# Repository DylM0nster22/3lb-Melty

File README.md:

# Unschuled dissasembly a 3lb "meltybrain" combat robot

This is a 3lb combat robot that me and luke have designed. this is a special type of robot thats way more complcated then normal bots, normal bots just have normal wheels and then the spinning weapon right well this bot is the weapon, the two hugely overpowered motors act as drive motors set to spin oppisite directions from eachother so the enitre 3lb mass of the robot is the weapon for a greater moi and impact. this can be achieved by using a microcontroller like a arduino nano or in my case a adafruint itsybitsy 32u4 and hooking it to the reciever and allowing it to act as a controller for the motor escs instead of the reciever and what is then does is edit the pwn that the escs get to allow translational drift to happen which is when even when the entire robot is spinning at 5000 rpm it can still go in a mostly stright line. 

# About this project 
This project includes a custom pcb for all the wiring of motors, escs, adafruit and the accelerometer. the pcb also acts as a power distrubution board which i struggled with for a while because of the amount of power going throught it, the back pads of the escs are going to be filled with solder to help conduct the electricity better and allow for more heat disspation. all the vias are also going to be filled to the brim with solder. i also created a reverse polarity protection circuit for the electronics other then the escs using a mosfet. the weapons are going to be made out of ar500 steel for the strength to weight ratio. the pcb is going to cost extra because it has to be 2oz copper, this was a fun and painful project to learn how to make pcbs on. i know buying spares of parts is frowned opon but its the same price without the spare weapon, i also left the carbon fibre out of the bom because theres not enough time to get it quoted.

| Parts                  | Amount | Cost   | Total Cost | Weight     | Total Weight | Provider                                                                                                                                                                                                                                                                                                                                                                                                                                                                                                                                                                                                                       |                                                                |
|------------------------|--------|--------|------------|------------|--------------|--------------------------------------------------------------------------------------------------------------------------------------------------------------------------------------------------------------------------------------------------------------------------------------------------------------------------------------------------------------------------------------------------------------------------------------------------------------------------------------------------------------------------------------------------------------------------------------------------------------------------------|----------------------------------------------------------------|
|                        |        |        |            |            |              |                                                                                                                                                                                                                                                                                                                                                                                                                                                                                                                                                                                                                                |                                                                |
| Drive/Weapon motor     | 2      | $34.59 | $69.18     | 156        | 312          | [HobbyKing](https://hobbyking.com/en_us/propdrive-v2-3542a-1250kv-brushless-outrunner-motor.html)                                                                                                                                                                                                                                                                                                                                                                                                                                                                                                                              | PROPDRIVE v2 3542 1250KV Brushless Outrunner Motor             |
| ESC                    | 2      | $30.00 | $60.00     | 13.9       | 27.8         | [Amazon](https://a.co/d/5kXJAQ6)                                                                                                                                                                                                                                                                                                                                                                                                                                                                                                                                                                                               | HGLRC Specter 90A 8S BLheli32 Single ESC                       |
| Battery                | 1      | $62.99 | $62.99     | 370        | 370          | [Amazon](https://www.amazon.com/OVONIC-Battery-3500mAh-14-8V-Connector/dp/B0DF1V1Z6P/?_encoding=UTF8&pd_rd_w=LSkKY&content-id=amzn1.sym.255b3518-6e7f-495c-8611-30a58648072e%3Aamzn1.symc.a68f4ca3-28dc-4388-a2cf-24672c480d8f&pf_rd_p=255b3518-6e7f-495c-8611-30a58648072e&pf_rd_r=3GX2SF0KEKYJ8BH71HKR&pd_rd_wg=qlzXY&pd_rd_r=9a85c712-36a2-43c4-88b3-a5dd3f800e3c&ref_=pd_hp_d_atf_ci_mcx_mr_ca_hp_atf_d)                                                                                                                                                                                                                   | OVONIC 4S LiPo Battery 3500mAh 14.8V 130C                      |
| Reciever               | 1      | $5.67  | $5.67      | 0.9        | 0.9          | [Aliexpress](https://www.aliexpress.us/item/3256804714662317.html?spm=a2g0o.cart.0.0.6c8138damJGm9i&mp=1&pdp_npi=5%40dis%21USD%21USD%206.16%21USD%206.16%21%21USD%204.16%21%21%21%402101ef7017504365178903148e6532%2112000030953927637%21ct%21US%212956977473%21%211%210&gatewayAdapt=glo2usa)                                                                                                                                                                                                                                                                                                                                 | FS2A 4CH AFHDS 2A                                              |
| Power switch           | 1      | $12.50 | $12.50     | 3          | 3            | [Repeat Robotics](https://repeat-robotics.com/buy/lynx-robot-switch/)                                                                                                                                                                                                                                                                                                                                                                                                                                                                                                                                                          | Lynx Anti-Spark Switch                                         |
| xt90 connector         | 1      | $12.99 | $12.99     | 18         | 36           | [Amazon](https://www.amazon.com/Yaohappy-Female-Bullet-Connectors-Battery/dp/B09L7GVWQ3?crid=2DGTJESIMJTI6&dib=eyJ2IjoiMSJ9.oj1eUX0K8K_T0ur2ZxRGOM_CHZcyffxqSc1sgTjLAVN_I8r0h-obcUxYasMM4pYiOT1-S7qvVRchCayMgTNkU9IHnSKHER11JB_SiyPN9TecKYbwlhtO-RVSU9PrwBjnGgEY4DYm6_s-GeH3TM9wyH8pjgsBidaMcXvCOAYD34LUtqNIVab5L0lMZO6SI-hlTBOQfHdTATIl4dHOiav3BXo8PqcrIy32ZCANfyBYoM-kYA9tz9-Rlfc7lQlCbdrgt_8ZJZdmC50YWCj4fq5Y0-1VINZfEkPBW9dsDkh7r4Y.p3LGtmhXeP_0f3tTEGv2Nu7CnV341Z1n8g0Of38vXMQ&dib_tag=se&keywords=xt180+connector&qid=1753072755&sprefix=xt180connector%2Caps%2C168&sr=8-13)                                             | xt90 connector                                                 |
| Buck Converter         | 1      | $3.55  | $3.55      | 3.85       | 3.85         | [Amazon](https://www.amazon.com/MEIVIFPV-Adjustable-Step-Down-Regulator-Quadcopter/dp/B0FCXTHX6W?crid=390TLPDTMMXZ5&dib=eyJ2IjoiMSJ9.1Jr64zcoS95A1rK3EBxNO3CJIyoZ79mjTwTGw-cGWwYzhsCjnwtq9tFKYtru7VslVwgn9NEwjFYUUAOIaBOdvRIIgADMhHxlZJw0nvxlIHNkWRB8i0TFbIHmy0jwz6bVKr2QxWyVsR5isN6o5xJ9p7NSM2FwncUvSvqxy9yQLel8lqT1HJv0LgqZMGddMUIMBy36P_skSL0CO1tlN3tN3l6ipZThyEs9flVcMkC-wLIvK8ZxHRQ3N3zzW-O-zwQPmJGyHZVmbPB7KdunM6jDycJsjYrUI3pfAjLhtyYeu1w.QzENFgkpZGmEwmCkBdKwvgVK3PpWlenEBpUwdHTDCyk&dib_tag=se&keywords=drone+regulator&qid=1753248899&sprefix=drone+regulato%2Caps%2C159&sr=8-7)                                     | Micro voltage regulator                                        |
| N-Channel mosfet       | 1      | $2.23 | $2.23     | negligible | negligible   | [Aliexpress](https://www.aliexpress.us/item/3256805136051666.html?spm=a2g0o.productlist.main.8.27ed2609oAbEZ7&algo_pvid=d6eaea9b-1818-4388-9122-a9396b72f46d&algo_exp_id=d6eaea9b-1818-4388-9122-a9396b72f46d-7&pdp_ext_f=%7B%22order%22%3A%225%22%2C%22eval%22%3A%221%22%7D&pdp_npi=6%40dis%21USD%212.23%212.23%21%21%2115.90%2115.90%21%402103241117544216774251366e2c2a%2112000032623433723%21sea%21US%212956977473%21X%211%210%21&curPageLogUid=rvZuV4hUFt88&utparam-url=scene%3Asearch%7Cquery_from%3A)                                                                                                                    | N-Channel Enhancement-Mode MOSFET Transistor 60V 115mA,SOT-23. |
| Accelerometer          | 1      | $25    | $25        | Unknown    | Unknown      | [Adafruit](https://www.adafruit.com/product/4627#technical-details)                                                                                                                                                                                                                                                                                                                                                                                                                                                                                                                                                            | Adafruit H3LIS331 Ultra High Range Triple-Axis Accelerometer   |
| Pin headers            | 1      | $1.68  | $1.68     | negligible | negligible   | [Aliexpress](https://www.aliexpress.us/item/2255800801798474.html?spm=a2g0o.productlist.main.1.7e4140cdhZ4fRh&algo_pvid=92aa51d4-414d-4073-8481-74f9170e3e0f&algo_exp_id=92aa51d4-414d-4073-8481-74f9170e3e0f-0&pdp_ext_f=%7B%22order%22%3A%221753%22%2C%22eval%22%3A%221%22%7D&pdp_npi=6%40dis%21USD%211.50%211.47%21%21%211.50%211.47%21%402101ef5e17544215568701003ea1fe%2110000013202368848%21sea%21US%212956977473%21X%211%210%21&curPageLogUid=oNsbEpczPk1e&utparam-url=scene%3Asearch%7Cquery_from%3A)                                                                                                                        | 40 pin Breakable Pin Header                                    |
| P-Channel mosfet       | 1      | $2.83  | $2.83      | negligible | negligible   | [Aliexpress](https://www.aliexpress.us/item/3256807719253034.html?productId=3256807719253034&selectedSkuId=12000042789419948&channel=detailPageDealCombineFloor&combineBizType=platformFreeShipping&intent_extra_sku_from=from_add_to_shopcart&type=mergeorder&pdp_npi=4%40dis%21USD%212.83%21%21%21%212.83%21%21%402101eac917531333647576521ef40e%2112000042789419948%21fus%21US%212956977473%21X&trackParams=%7B%22businessScenario%22%3A%22choiceV2%22%2C%22activityType%22%3A%22CHOICE_FREE_SHIPPING%22%7D&spm=a2g0o.detail.fusionpage.0&gatewayAdapt=glo2usa)                                                             | SUM110P06-07L-E3 p channel mosfet                              |
| Blue LED               | 1      | $ 3.68 | $3.68      | 2.8        | 2.8          | [Aliexpress](https://www.aliexpress.us/item/3256803137393104.html?spm=a2g0o.productlist.main.4.6ec9llDBllDB7Q&aem_p4p_detail=202508022044181770915020208280005830057&algo_pvid=d7b2affc-a5fc-4cad-83a2-7c0d2d7caf38&algo_exp_id=d7b2affc-a5fc-4cad-83a2-7c0d2d7caf38-3&pdp_ext_f=%7B%22order%22%3A%22913%22%2C%22eval%22%3A%221%22%7D&pdp_npi=4%40dis%21USD%213.88%213.68%21%21%213.88%213.68%21%402101c80017541926584706554e918c%2112000025211444658%21sea%21US%212956977473%21X&curPageLogUid=JX9L9FsJ3aNU&utparam-url=scene%3Asearch%7Cquery_from%3A&search_p4p_id=202508022044181770915020208280005830057_1)               | Clear blue LED Diode Lights                                    |
| Zener Diode            | 1      | $2.02  | $2.02      | negligible | negligible   | [Aliexpress](https://www.aliexpress.us/item/3256807042309359.html?spm=a2g0o.productlist.main.3.63b223e0PyMMgl&algo_pvid=0ef8bae5-e9ff-4628-8746-641cc5e44014&algo_exp_id=0ef8bae5-e9ff-4628-8746-641cc5e44014-2&pdp_ext_f=%7B%22order%22%3A%221039%22%2C%22eval%22%3A%221%22%7D&pdp_npi=4%40dis%21USD%212.02%212.02%21%21%2114.52%2114.52%21%402101eab017541930522785029e2719%2112000039883986340%21sea%21US%212956977473%21X&curPageLogUid=F3EWyYFjvbFn&utparam-url=scene%3Asearch%7Cquery_from%3A)                                                                                                                           | 15v zener diode                                                |
| Resistor set           | 1      | $2.18     | $2.18         | negligible | negligible   | [Aliexpress](https://www.aliexpress.us/item/3256807449715737.html?spm=a2g0o.productlist.main.1.17ff67a4AzyDFQ&algo_pvid=a82b51df-5cc7-4f57-b865-6a39c8be97f2&algo_exp_id=a82b51df-5cc7-4f57-b865-6a39c8be97f2-0&pdp_ext_f=%7B%22order%22%3A%222496%22%2C%22spu_best_type%22%3A%22price%22%2C%22eval%22%3A%221%22%2C%22orig_sl_item_id%22%3A%221005007636030489%22%2C%22orig_item_id%22%3A%221005008498514164%22%7D&pdp_npi=6%40dis%21USD%214.75%212.18%21%21%2133.94%2115.61%21%402103244b17544208839038015e5c76%2112000041589931297%21sea%21US%212956977473%21X%211%210%21&curPageLogUid=pNiEIzsiGovf&utparam-url=scene%3Asearch%7Cquery_from%3A#nav-specification) | 0805 Chip Resistor Assortment Kit                              |
| Ceramic Capacitor 47uf | 1      | $2.62  | $2.62      | negligible | negligible   | [Aliexpress](https://www.aliexpress.us/item/3256805862294240.html?spm=a2g0o.productlist.main.13.7051FfzkFfzkL0&algo_pvid=792518e9-9dcc-4c64-9aa3-2b24fc632cb1&algo_exp_id=792518e9-9dcc-4c64-9aa3-2b24fc632cb1-12&pdp_ext_f=%7B%22order%22%3A%2241%22%2C%22eval%22%3A%221%22%7D&pdp_npi=4%40dis%21USD%212.40%212.40%21%21%2117.11%2117.11%21%402101c5ac17531350387723905e8d00%2112000035487304923%21sea%21US%212956977473%21X&curPageLogUid=fM4JkQhXOSfn&utparam-url=scene%3Asearch%7Cquery_from%3A)                                                                                                                           | 0805 47UF 25V X7R M                                            |
| Electrolytic Capacitor | 1      | $3.64     | $3.64         | 33         | 33           | [Aliexpress](https://www.aliexpress.us/item/3256802246707783.html?spm=a2g0o.productlist.main.2.5c212S4g2S4gj2&algo_pvid=e10b7241-16d0-45bf-b4d6-bcaa89671bd0&algo_exp_id=e10b7241-16d0-45bf-b4d6-bcaa89671bd0-1&pdp_ext_f=%7B%22order%22%3A%2245%22%2C%22eval%22%3A%221%22%7D&pdp_npi=6%40dis%21USD%212.19%212.19%21%21%212.19%212.19%21%402101d9ef17544207172598208eb3f3%2112000034697160097%21sea%21US%212956977473%21X%211%210%21&curPageLogUid=z2iWJShEubXI&utparam-url=scene%3Asearch%7Cquery_from%3A)                                                                                                              | 4700uF 35V 18x30mm Electrolytic Capacitor                      |
| 0.1UF Caps             | 1      | $2.6   | $2.6       | negligible | negligible   | [Aliexpress](https://www.aliexpress.us/item/3256806974673655.html?spm=a2g0o.productlist.main.4.2a163d6c6GFNlt&aem_p4p_detail=20250802223341830896677241460006022743&algo_pvid=f77c6a61-7a33-4277-b55d-be178839fe80&algo_exp_id=f77c6a61-7a33-4277-b55d-be178839fe80-3&pdp_ext_f=%7B%22order%22%3A%22362%22%2C%22eval%22%3A%221%22%7D&pdp_npi=4%40dis%21USD%212.58%212.58%21%21%2118.50%2118.50%21%402101c80017541992210352378e9188%2112000039654696631%21sea%21US%212956977473%21X&curPageLogUid=gLQemuFYhD8R&utparam-url=scene%3Asearch%7Cquery_from%3A&search_p4p_id=20250802223341830896677241460006022743_1)               |                                                                |
| ATMEGA32U4-AU          | 2      | $4.11  | 8.22       | negligible | negligible   | [Aliexpress](https://www.aliexpress.us/item/3256808047819136.html?spm=a2g0o.productlist.main.17.34463ce6l0mbeJ&algo_pvid=e141f10a-4004-43fc-9fc0-35545c941355&algo_exp_id=e141f10a-4004-43fc-9fc0-35545c941355-16&pdp_ext_f=%7B%22order%22%3A%2230%22%2C%22eval%22%3A%221%22%7D&pdp_npi=4%40dis%21USD%218.15%214.11%21%21%2158.50%2129.51%21%40210308a417541952258271789ede9e%2112000044321081291%21sea%21US%212956977473%21X&curPageLogUid=svPYm9ausJuG&utparam-url=scene%3Asearch%7Cquery_from%3A)                                                                                                                           |                                                                |
| 22PF Caps              | 1      | $2.6   | $2.6       | negligible | negligible   | [Aliexpress](https://www.aliexpress.us/item/3256806974673655.html?spm=a2g0o.productlist.main.4.2a163d6c6GFNlt&aem_p4p_detail=20250802223341830896677241460006022743&algo_pvid=f77c6a61-7a33-4277-b55d-be178839fe80&algo_exp_id=f77c6a61-7a33-4277-b55d-be178839fe80-3&pdp_ext_f=%7B%22order%22%3A%22362%22%2C%22eval%22%3A%221%22%7D&pdp_npi=4%40dis%21USD%212.58%212.58%21%21%2118.50%2118.50%21%402101c80017541992210352378e9188%2112000039654696631%21sea%21US%212956977473%21X&curPageLogUid=gLQemuFYhD8R&utparam-url=scene%3Asearch%7Cquery_from%3A&search_p4p_id=20250802223341830896677241460006022743_1)               |                                                                |
| Ceramic Capacitor 10UF | 1      | $2.62  | $2.62      | negligible | negligible   | [Aliexpress](https://www.aliexpress.us/item/3256805862294240.html?spm=a2g0o.productlist.main.13.7051FfzkFfzkL0&algo_pvid=792518e9-9dcc-4c64-9aa3-2b24fc632cb1&algo_exp_id=792518e9-9dcc-4c64-9aa3-2b24fc632cb1-12&pdp_ext_f=%7B%22order%22%3A%2241%22%2C%22eval%22%3A%221%22%7D&pdp_npi=4%40dis%21USD%212.40%212.40%21%21%2117.11%2117.11%21%402101c5ac17531350387723905e8d00%2112000035487304923%21sea%21US%212956977473%21X&curPageLogUid=fM4JkQhXOSfn&utparam-url=scene%3Asearch%7Cquery_from%3A)                                                                                                                           | 0805 47UF 25V X7R M)                                           |
| 10NF Caps              | 1      | $2.6   | $2.6       | negligible | negligible   | [Aliexpress](https://www.aliexpress.us/item/3256806974673655.html?spm=a2g0o.productlist.main.4.2a163d6c6GFNlt&aem_p4p_detail=20250802223341830896677241460006022743&algo_pvid=f77c6a61-7a33-4277-b55d-be178839fe80&algo_exp_id=f77c6a61-7a33-4277-b55d-be178839fe80-3&pdp_ext_f=%7B%22order%22%3A%22362%22%2C%22eval%22%3A%221%22%7D&pdp_npi=4%40dis%21USD%212.58%212.58%21%21%2118.50%2118.50%21%402101c80017541992210352378e9188%2112000039654696631%21sea%21US%212956977473%21X&curPageLogUid=gLQemuFYhD8R&utparam-url=scene%3Asearch%7Cquery_from%3A&search_p4p_id=20250802223341830896677241460006022743_1)               |                                                                |
| USB-C-PORT             | 1      | $1.43  | 1.43       | negligible | negligible   | [Aliexpress](https://www.aliexpress.us/item/3256808618842348.html?spm=a2g0o.productlist.main.14.12d1AEEQAEEQf1&algo_pvid=f1e252ce-79f0-40bc-a208-9dad4d67d717&algo_exp_id=f1e252ce-79f0-40bc-a208-9dad4d67d717-13&pdp_ext_f=%7B%22order%22%3A%228%22%2C%22eval%22%3A%221%22%7D&pdp_npi=4%40dis%21USD%211.43%211.43%21%21%211.43%211.43%21%402101ec1a17542010304474624efe22%2112000046734917627%21sea%21US%212956977473%21X&curPageLogUid=ZmTTn6srn0mK&utparam-url=scene%3Asearch%7Cquery_from%3A)                                                                                                                              |                                                                |
| USBLC6-4SC6            | 1      | $0.84  | $0.84      | negligible | negligible   | [Aliexpress](https://www.aliexpress.us/item/3256807215523812.html?spm=a2g0o.productlist.main.3.783b3768OPuHmo&algo_pvid=10558e09-68cb-4043-8a8e-b1738d8b1b68&algo_exp_id=10558e09-68cb-4043-8a8e-b1738d8b1b68-2&pdp_ext_f=%7B%22order%22%3A%225%22%2C%22eval%22%3A%221%22%7D&pdp_npi=4%40dis%21USD%210.85%210.84%21%21%210.85%210.84%21%402101c5b217542011445637866e24e0%2112000040592641332%21sea%21US%212956977473%21X&curPageLogUid=I4eNGBENROK1&utparam-url=scene%3Asearch%7Cquery_from%3A)                                                                                                                                |                                                                |
| Weapon                 | 3      | $10    | $31        |            |              | [SendCutSend](                                                                                                                                                                                                                                                                                                                                                                                                                                                                                                                                                                                                                 | ar500 steel weapon                                             |
| PCB                    | 1      | $27.50 | $27.50     |            |              | [JLCPCB](                                                                                                                                                                                                                                                                                                                                                                                                                                                                                                                                                                                                                      | pcb for power distrubution and connections to mcu and escs     |
|                        |        |        |            |            |              |                                                                                                                                                                                                                                                                                                                                                                                                                                                                                                                                                                                                                                |                                                                |
| Body                   | 1      | $0.00  | $0.00      |       |       |                                                                                                                                                                                                                                                                                                                                                                                                                                                                                                                                                                                                                                |                                                                |
|                        |        |        | $352.17    |            | 1175.95      |                                                                                                                                                                                                                                                                                                                                                                                                                                                                                                                                                                                                                                |                                                                |

source for code https://github.com/nothinglabs/openmelt2

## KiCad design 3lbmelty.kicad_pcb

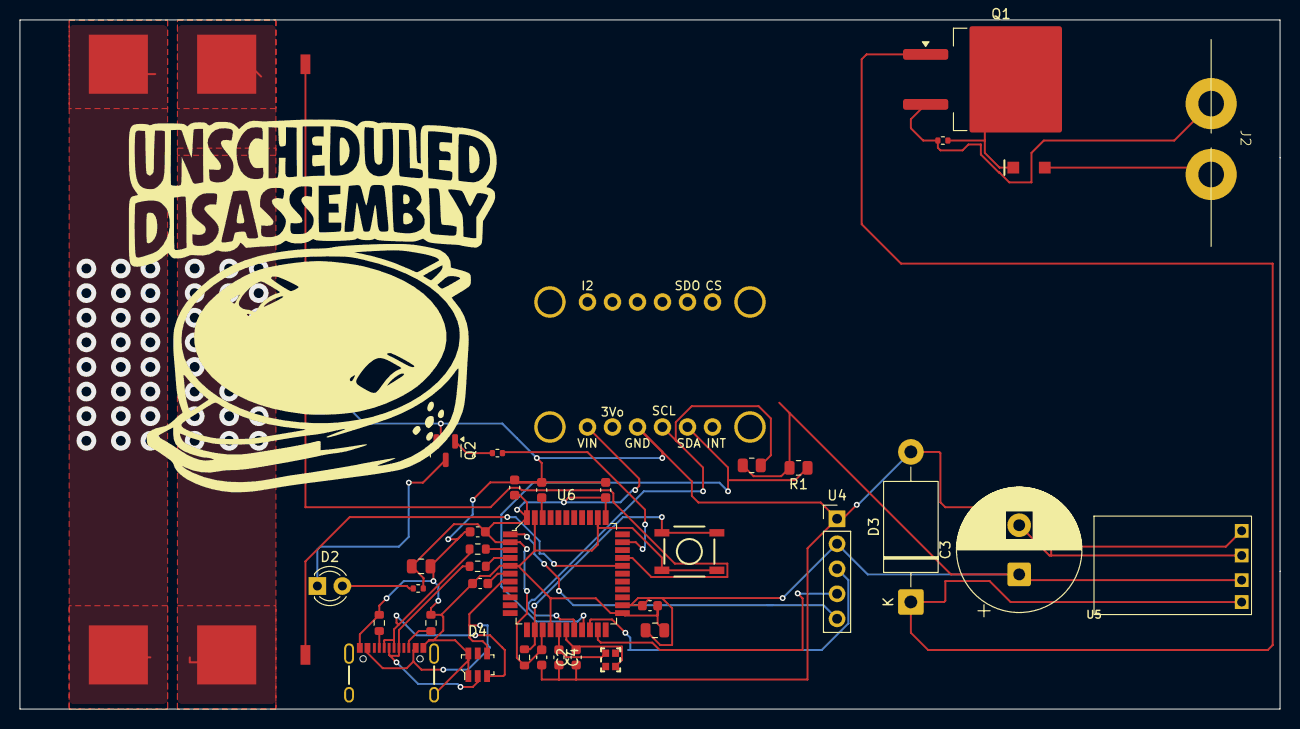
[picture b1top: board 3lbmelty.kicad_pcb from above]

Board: 2 copper layers, 128.0 x 70.0 mm, 38 parts (0 on the bottom side), 28 nets.

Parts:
C1: 47uF; C_0805_2012Metric
C1#2, C5, C6, C7, C8, C9: 0.1uF; C_0603_1608Metric
C2, C4: 22pF; C_0603_1608Metric
C3: 4700uF; CP_Radial_D12.5mm_P5.00mm
C11: 10uF; C_0805_2012Metric
C12: 10nF; C_0603_1608Metric
D1: D_Zener; SOD-123
D2: Blue LED ~ 3.5v / 20ma; LED_D3.0mm
D3: 1.5KExxA; D_DO-201AE_P15.24mm_Horizontal
D4: USBLC6-4SC6; SOT23-6L
J1: Esc 2; ESC
J2: Amass_XT90-S; Amass_XT60PW
J3: Esc 1; ESC
J4: USB_C_Receptacle; USB-C_16
Q1: SUM110P06-07L-E3; TO-263-2
Q2: 2N7002; SOT-23
R1, R2: 4.7k; R_0805_2012Metric
R3: 10k; R_0402_1005Metric
R4: 1k; R_0402_1005Metric
R5: 150; R_0402_1005Metric
R6, R7: 22; R_0603_1608Metric
R8: 10k; R_0603_1608Metric
R9, R10: 5.1k; R_0603_1608Metric
SW1: SMD_5.2x5.2mm_h1.5mm; Push_SMD_5.2x5.2mm_h1.9mm
U2: Adafruit_H3LIS311_Breakout; h3
U4: RC_RECEIVER; PinHeader_1x05_P2.54mm_Vertical
U5: BUCK_CONVERTER; MP1584
U6: ATMEGA32U4-AU; TQFP-44_10x10mm
Y1: 16MHz; Crystal_SMD_2.0x1.6mm

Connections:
5v: C1.1, C3.1, C5.2, C6.1, C7.1, C8.1, C9.1, C11.1, R1.2, R2.2, R5.1, R8.1, U2.1 (VIN), U4.2 (+V), U5.OUT+, U6.2 (UVCC), U6.14 (VCC), U6.24 (AVCC), U6.34 (VCC), U6.44 (AVCC)
BAT: J1.1, J2.1, J3.1, Q1.3 (S), R3.2
BAT_SAFE: D3.1 (A1), Q1.1 (D), U5.IN+
D+: D4.2, J4.A6 (D+), J4.B6 (D+), R6.1
D-: D4.3, J4.A7 (D-), J4.B7 (D-), R7.1
GND: C1.2, C1#2.1, C2.1, C3.2, C4.2, C5.1, C6.2, C7.2, C8.2, C9.2, C11.2, C12.2, D1.2 (A), D3.2 (A2), D4.1, D4.6, J1.3, J2.2, J3.3, J4.GND, J4.S (SHIELD), Q2.2 (S), R9.2, R10.1, SW1.2, U2.3 (GND), U4.1 (GND), U5.IN-, U5.OUT-, U6.5 (UGND), U6.15 (GND), U6.23 (GND), U6.35 (GND), U6.43 (GND)
MOTOR_1: J3.2, U6.29 (PB5)
MOTOR_2: J1.2, U6.30 (PB6)
unnamed: D1.1 (K), Q1.2 (G), R3.1
unnamed: D2.2 (A), R5.2
unnamed: D2.1 (K), Q2.3 (D)
unnamed: J4.A5 (CC1), R9.1
unnamed: J4.B5 (CC2), R10.2
unnamed: Q2.1 (G), R4.2
unnamed: C1#2.2, U6.42 (AREF)
unnamed: R6.2, U6.4 (D+)
unnamed: R7.2, U6.3 (D-)
unnamed: R4.1, U6.32 (PC7)
unnamed: C12.1, U6.6 (UCAP)
unnamed: C2.2, U6.17 (XTAL1), Y1.1
unnamed: C4.1, U6.16 (XTAL2), Y1.2
RC1: U4.5 (CH1), U6.1 (PE6)
RC2: U4.4 (CH2), U6.21 (PD3)
RC3: U4.3 (CH3), U6.20 (PD2)
Reset: R8.2, SW1.1, U6.13 (~RES)
SCL: R2.1, U2.4 (SCL), U6.18 (PD0)
SDA: R1.1, U2.5 (SDA), U6.19 (PD1)
VBUS: D4.4, J4.VBUS, U6.7 (VBUS)

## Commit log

2025-07-29 adding .step and code
2025-07-30 added pcb files
2025-08-03 new pcb
2025-08-03 fixed small issue with resistor placement
